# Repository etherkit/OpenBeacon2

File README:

Documentation for the OpenBeacon Mini Multimode MEPT, which is based on the OpenBeacon project.

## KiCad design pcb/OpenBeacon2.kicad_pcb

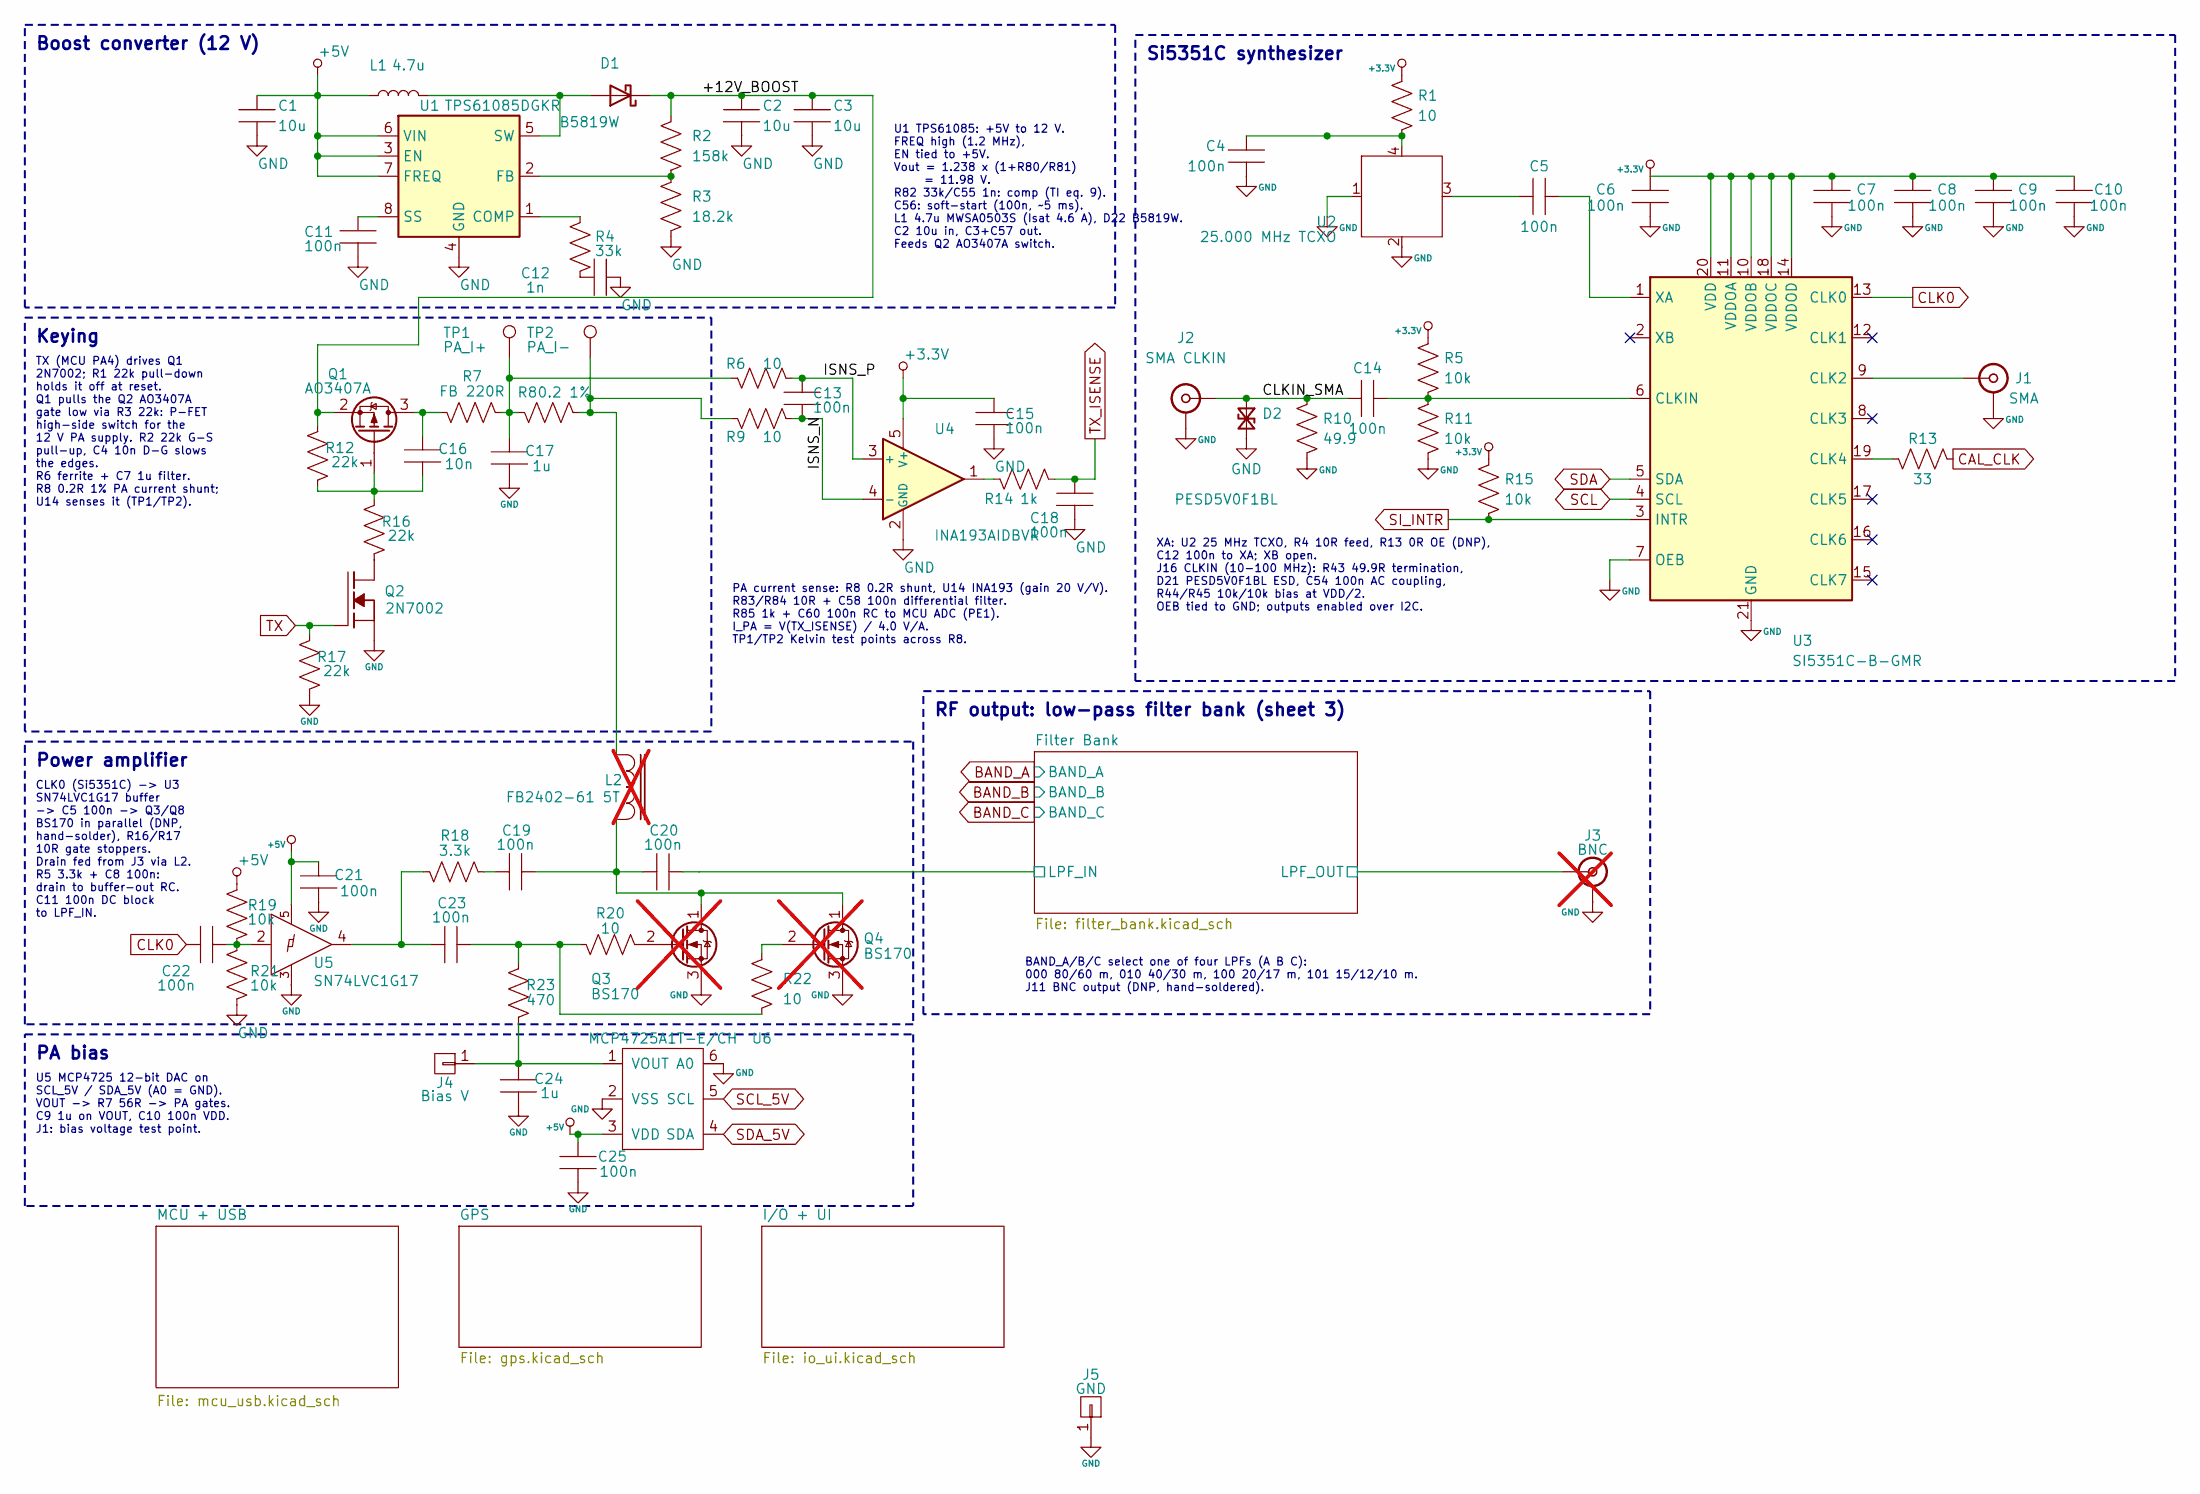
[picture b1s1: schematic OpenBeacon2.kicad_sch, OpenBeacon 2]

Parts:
C1: 10u; C_0805_2012Metric; MPN CL21A106KAYNNNE; LCSC C15850
C2, C3: 10u; C_1206_3216Metric; MPN CL31A106KBHNNNE; LCSC C13585
C4, C5, C19, C20, C21, C23, C25: 100n; C_0805_2012Metric; MPN CC0805KRX7R9BB104; LCSC C49678
C6: 100n; C_0402_1005Metric; MPN CL05B104KO5NNNC; LCSC C1525
C7, C8, C9, C10, C14: 100n; C_0603_1608Metric; MPN CL10B104KB8NNNC; LCSC C1591
C11, C13, C15, C18, C22: 100n; C_0603_1608Metric; MPN CC0603KRX7R9BB104; LCSC C14663
C12: 1n; C_0603_1608Metric; MPN CL10B102KB8NNNC; LCSC C1588
C16: 10n; C_0805_2012Metric; MPN CL21B103KBANNNC; LCSC C1710
C17, C24: 1u; C_0805_2012Metric; MPN CL21B105KBFNNNE; LCSC C28323
D1: B5819W; D_SOD-123; MPN B5819W SL; LCSC C8598
D2: PESD5V0F1BL; D_SOD-882; MPN PESD5V0F1BL,315; LCSC C45961
J1: SMA; SMA-ENDLAUNCH; MPN BWSMA-KE-P001; LCSC C496550
J2: SMA CLKIN; SMA-ENDLAUNCH; MPN BWSMA-KE-P001; LCSC C496550
J3: BNC; BNC-AMPHENOL-31-5431-10RFX; MPN 031-5431-10RFX; LCSC C6956217; not fitted
J4: Bias V; Measurement_Point_Square-TH_Small
J5: GND; Measurement_Point_Square-TH_Small
L1: 4.7u; L_Sunlord_MWSA0503S; MPN MWSA0503S-4R7MT; LCSC C408410
L2: FB2402-61 5T; BN2402; MPN 2843002402; not fitted
Q1: AO3407A; SOT23-MMBT440X; MPN AO3407A; LCSC C15155
Q2: 2N7002; SOT23-2N7002; MPN 2N7002; LCSC C8545
Q3, Q4: BS170; TO-92_Inline; MPN BS170; LCSC C111691; not fitted
R1: 10; R_0805_2012Metric; MPN 0805W8F100JT5E; LCSC C17415
R2: 158k; R_0603_1608Metric; MPN 0603WAF1583T5E; LCSC C22883
R3: 18.2k; R_0603_1608Metric; MPN 0603WAF1822T5E; LCSC C22892
R4: 33k; R_0603_1608Metric; MPN 0603WAF3302T5E; LCSC C4216
R5, R11, R15, R19, R21: 10k; R_0603_1608Metric; MPN 0603WAF1002T5E; LCSC C25804
R6, R9, R20, R22: 10; R_0603_1608Metric; MPN 0603WAF100JT5E; LCSC C22859
R7: FB 220R; L_0603_1608Metric; MPN BLM18PG221SN1D; LCSC C80165
R8: 0.2 1%; R_0805_2012Metric; MPN 0805W8F200LT5E; LCSC C44051
R10: 49.9; R_0603_1608Metric; MPN 0603WAF499JT5E; LCSC C23185
R12, R16, R17: 22k; R_0805_2012Metric; MPN 0805W8F2202T5E; LCSC C17560
R13: 33; R_0603_1608Metric; MPN 0603WAF330JT5E; LCSC C23140
R14: 1k; R_0603_1608Metric; MPN 0603WAF1001T5E; LCSC C21190
R18: 3.3k; R_0805_2012Metric; MPN 0805W8F3301T5E; LCSC C26010
R23: 470; R_0805_2012Metric; MPN 0805W8F4700T5E; LCSC C17710
TP1: PA_I+; Measurement_Point_Square-TH_Small
TP2: PA_I-; Measurement_Point_Square-TH_Small
U1: TPS61085DGKR; VSSOP-8_3x3mm_P0.65mm; MPN TPS61085DGKR; LCSC C113659
U2: 25.000 MHz TCXO; ASTX-H11-25.000MHZ-T; MPN OW2EL89CENUXK7YLC-25M; LCSC C48888230
U3: SI5351C-B-GMR; QFN-20-1EP_4x4mm_P0.5mm_EP2.7x2.7mm; MPN SI5351C-B-GMR; LCSC C2649375
U4: INA193AIDBVR; SOT-23-5; MPN INA193AIDBVR; LCSC C19548
U5: SN74LVC1G17; SOT23-5; MPN SN74LVC1G17DBVR; LCSC C7836
U6: MCP4725A1T-E/CH; SOT23-6; MPN MCP4725A1T-E/CH; LCSC C61423

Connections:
+3.3V: C6.1, C7.1, C8.1, C9.1, C10.1, C15.1, R1.1, R5.1, R15.1, U3.10 (VDDOB), U3.11 (VDDOA), U3.14 (VDDOD), U3.18 (VDDOC), U3.20 (VDD), U4.5 (V+); also elsewhere on the board
+5V: C1.1, C21.1, C25.1, L1.1, R19.1, U1.3 (EN), U1.6 (VIN), U1.7 (FREQ), U5.5 (VCC), U6.3 (VDD); also elsewhere on the board
/+12V_BOOST: C2.1, C3.1, D1.1 (K), Q1.2 (S), R2.1, R12.1
/CLKIN_SMA: C14.1, D2.1 (A1), J2.1 (In), R10.1
/Filter Bank/LPF_IN: C20.1; also elsewhere on the board
/Filter Bank/LPF_OUT: J3.1 (In); also elsewhere on the board
/ISNS_N: C13.2, R9.2, U4.4 (-)
/ISNS_P: C13.1, R6.2, U4.3 (+)
CAL_CLK: R13.2; also elsewhere on the board
CLK0: C22.1, U3.13 (CLK0)
GND: C1.2, C2.2, C3.2, C4.2, C6.2, C7.2, C8.2, C9.2, C10.2, C11.2, C12.2, C15.2, C17.2, C18.2, C21.2, C24.2, C25.2, D2.2 (A2), J1.2 (Ext), J2.2 (Ext), J3.2 (Ext), J5.1, Q2.1 (S), Q3.3 (S), Q4.3 (S), R3.2, R10.2, R11.2, R17.2, R21.2, U1.4 (GND), U2.1 (GND), U2.2 (GND), U3.7 (OEB), U3.21 (GND), U4.2 (GND), U5.3 (GND), U6.2 (VSS), U6.6 (A0); also elsewhere on the board
unnamed: C12.1, R4.2
unnamed: C17.1, R6.1, R7.1, R8.2, TP1.1
unnamed: C19.2, R18.1
unnamed: C22.2, R19.2, R21.1, U5.2
unnamed: C23.1, R20.1, R22.2, R23.1
unnamed: C23.2, R18.2, U5.4
unnamed: D1.2 (A), L1.2, U1.5 (SW)
unnamed: J1.1 (In), U3.9 (CLK2)
unnamed: C24.1, J4.1, R23.2, U6.1 (VOUT)
unnamed: L2.1, R8.1, R9.1, TP2.1
unnamed: C16.1, Q1.3 (D), R7.2
unnamed: C16.2, Q1.1 (G), R12.2, R16.1
unnamed: Q2.3 (D), R16.2
unnamed: C19.1, C20.2, L2.2, Q3.1 (D), Q4.1 (D)
unnamed: Q3.2 (G), R20.2
unnamed: Q4.2 (G), R22.1
unnamed: R14.1, U4.1
unnamed: R4.1, U1.1 (COMP)
unnamed: R2.2, R3.1, U1.2 (FB)
unnamed: C11.1, U1.8 (SS)
unnamed: C5.1, U2.3 (OUT)
unnamed: C4.1, R1.2, U2.4 (VDD)
unnamed: R13.1, U3.19 (CLK4)
unnamed: C14.2, R5.2, R11.1, U3.6 (CLKIN)
unnamed: C5.2, U3.1 (XA)
SCL: U3.4 (SCL); also elsewhere on the board
SCL_5V: U6.5 (SCL); also elsewhere on the board
SDA: U3.5 (SDA); also elsewhere on the board
SDA_5V: U6.4 (SDA); also elsewhere on the board
SI_INTR: R15.2, U3.3 (INTR); also elsewhere on the board
TX: Q2.2 (G), R17.1; also elsewhere on the board
TX_ISENSE: C18.1, R14.2; also elsewhere on the board

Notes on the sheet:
Boost converter (12 V)
Keying
TX (MCU PA4) drives Q1 2N7002; R1 22k pull-down holds it off at reset. Q1 pulls the Q2 AO3407A gate low via R3 22k: P-FET high-side switch for the 12 V PA supply. R2 22k G-S pull-up, C4 10n D-G slows the edges. R6 ferrite + C7 1u filter. R8 0.2R 1% PA current shunt; U14 senses it (TP1/TP2).
Power amplifier
CLK0 (Si5351C) -> U3 SN74LVC1G17 buffer -> C5 100n -> Q3/Q8 BS170 in parallel (DNP, hand-solder), R16/R17 10R gate stoppers. Drain fed from J3 via L2. R5 3.3k + C8 100n: drain to buffer-out RC. C11 100n DC block to LPF_IN.
PA bias
U5 MCP4725 12-bit DAC on SCL_5V / SDA_5V (A0 = GND). VOUT -> R7 56R -> PA gates. C9 1u on VOUT, C10 100n VDD. J1: bias voltage test point.
Si5351C synthesizer
XA: U2 25 MHz TCXO, R4 10R feed, R13 0R OE (DNP), C12 100n to XA; XB open. J16 CLKIN (10-100 MHz): R43 49.9R termination, D21 PESD5V0F1BL ESD, C54 100n AC coupling, R44/R45 10k/10k bias at VDD/2. OEB tied to GND; outputs enabled over I2C.
RF output: low-pass filter bank (sheet 3)
BAND_A/B/C select one of four LPFs (A B C): 000 80/60 m, 010 40/30 m, 100 20/17 m, 101 15/12/10 m. J11 BNC output (DNP, hand-soldered).
U1 TPS61085: +5V to 12 V. FREQ high (1.2 MHz), EN tied to +5V. Vout = 1.238 x (1+R80/R81) = 11.98 V. R82 33k/C55 1n: comp (TI eq. 9). C56: soft-start (100n, ~5 ms). L1 4.7u MWSA0503S (Isat 4.6 A), D22 B5819W. C2 10u in, C3+C57 out. Feeds Q2 AO3407A switch.
PA current sense: R8 0.2R shunt, U14 INA193 (gain 20 V/V). R83/R84 10R + C58 100n differential filter. R85 1k + C60 100n RC to MCU ADC (PE1). I_PA = V(TX_ISENSE) / 4.0 V/A. TP1/TP2 Kelvin test points across R8.

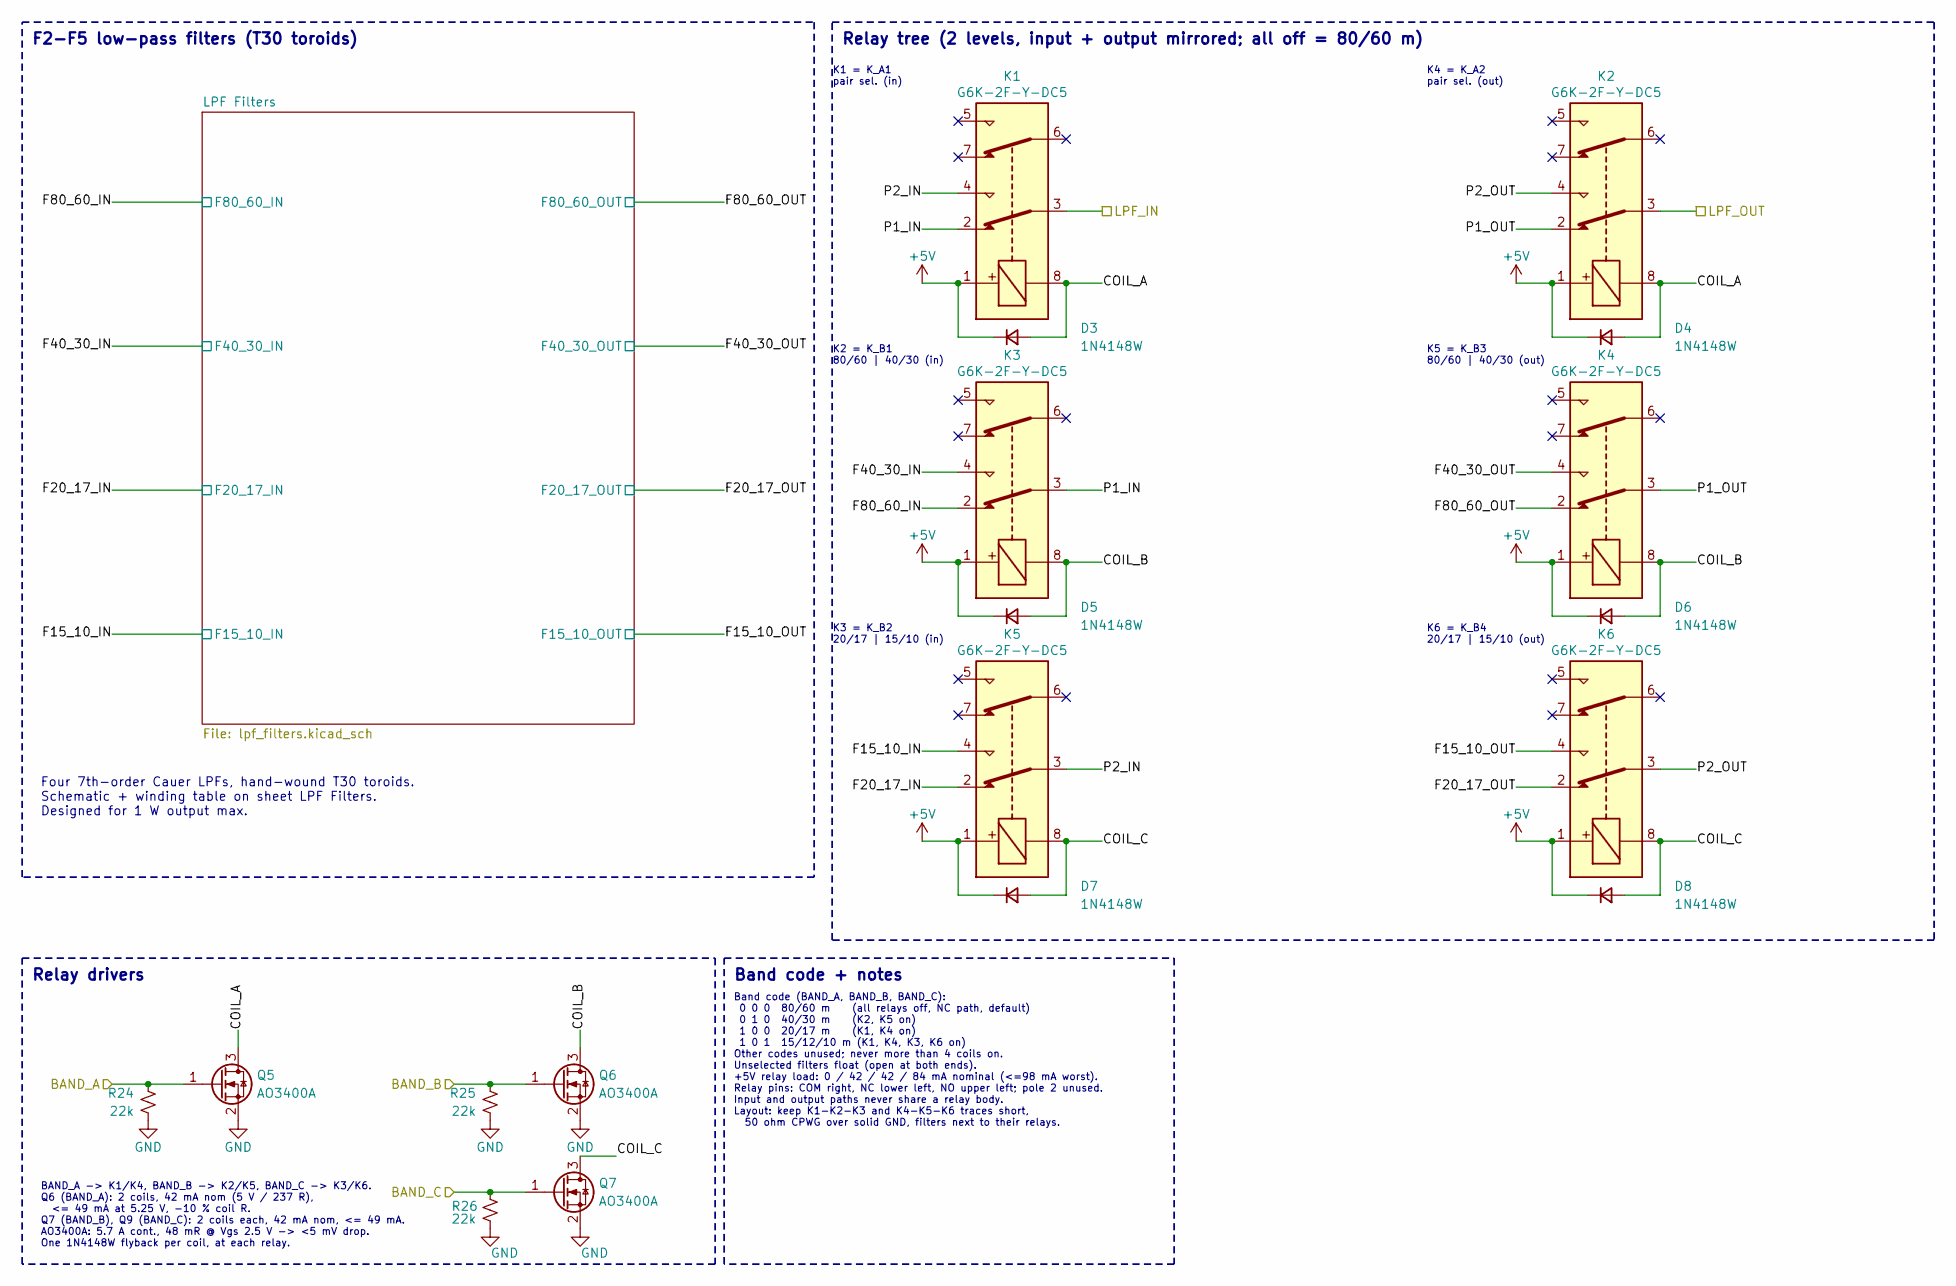
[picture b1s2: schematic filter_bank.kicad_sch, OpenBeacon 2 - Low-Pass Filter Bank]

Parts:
D3, D4, D5, D6, D7, D8: 1N4148W; D_SOD-123; MPN 1N4148W; LCSC C81598
K1, K2, K3, K4, K5, K6: G6K-2F-Y-DC5; Relay_DPDT_Omron_G6K-2F-Y; MPN G6K-2F-Y-DC5; LCSC C326376
Q5, Q6, Q7: AO3400A; SOT-23; MPN AO3400A; LCSC C20917
R24, R25, R26: 22k; R_0603_1608Metric; MPN 0603WAF2202T5E; LCSC C31850

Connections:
+5V: D3.1 (K), D4.1 (K), D5.1 (K), D6.1 (K), D7.1 (K), D8.1 (K), K1.1, K2.1, K3.1, K4.1, K5.1, K6.1; also elsewhere on the board
/Filter Bank/COIL_A: D3.2 (A), D4.2 (A), K1.8, K2.8, Q5.3 (D)
/Filter Bank/COIL_B: D5.2 (A), D6.2 (A), K3.8, K4.8, Q6.3 (D)
/Filter Bank/COIL_C: D7.2 (A), D8.2 (A), K5.8, K6.8, Q7.3 (D)
/Filter Bank/F15_10_IN: K5.4; also elsewhere on the board
/Filter Bank/F15_10_OUT: K6.4; also elsewhere on the board
/Filter Bank/F20_17_IN: K5.2; also elsewhere on the board
/Filter Bank/F20_17_OUT: K6.2; also elsewhere on the board
/Filter Bank/F40_30_IN: K3.4; also elsewhere on the board
/Filter Bank/F40_30_OUT: K4.4; also elsewhere on the board
/Filter Bank/F80_60_IN: K3.2; also elsewhere on the board
/Filter Bank/F80_60_OUT: K4.2; also elsewhere on the board
/Filter Bank/LPF_IN: K1.3; also elsewhere on the board
/Filter Bank/LPF_OUT: K2.3; also elsewhere on the board
/Filter Bank/P1_IN: K1.2, K3.3
/Filter Bank/P1_OUT: K2.2, K4.3
/Filter Bank/P2_IN: K1.4, K5.3
/Filter Bank/P2_OUT: K2.4, K6.3
BAND_A: Q5.1 (G), R24.1; also elsewhere on the board
BAND_B: Q6.1 (G), R25.1; also elsewhere on the board
BAND_C: Q7.1 (G), R26.1; also elsewhere on the board
GND: Q5.2 (S), Q6.2 (S), Q7.2 (S), R24.2, R25.2, R26.2; also elsewhere on the board

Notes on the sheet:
Relay tree (2 levels, input + output mirrored; all off = 80/60 m)
K1 = K_A1 pair sel. (in)
K2 = K_B1 80/60 | 40/30 (in)
K3 = K_B2 20/17 | 15/10 (in)
K4 = K_A2 pair sel. (out)
K5 = K_B3 80/60 | 40/30 (out)
K6 = K_B4 20/17 | 15/10 (out)
Relay drivers
Band code + notes
BAND_A -> K1/K4, BAND_B -> K2/K5, BAND_C -> K3/K6. Q6 (BAND_A): 2 coils, 42 mA nom (5 V / 237 R), <= 49 mA at 5.25 V, -10 % coil R. Q7 (BAND_B), Q9 (BAND_C): 2 coils each, 42 mA nom, <= 49 mA. AO3400A: 5.7 A cont., 48 mR @ Vgs 2.5 V -> <5 mV drop. One 1N4148W flyback per coil, at each relay.
Band code (BAND_A, BAND_B, BAND_C): 0 0 0 80/60 m (all relays off, NC path, default) 0 1 0 40/30 m (K2, K5 on) 1 0 0 20/17 m (K1, K4 on) 1 0 1 15/12/10 m (K1, K4, K3, K6 on) Other codes unused; never more than 4 coils on. Unselected filters float (open at both ends). +5V relay load: 0 / 42 / 42 / 8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
F2-F5 low-pass filters (T30 toroids)
Four 7th-order Cauer LPFs, hand-wound T30 toroids. Schematic + winding table on sheet LPF Filters. Designed for 1 W output max.

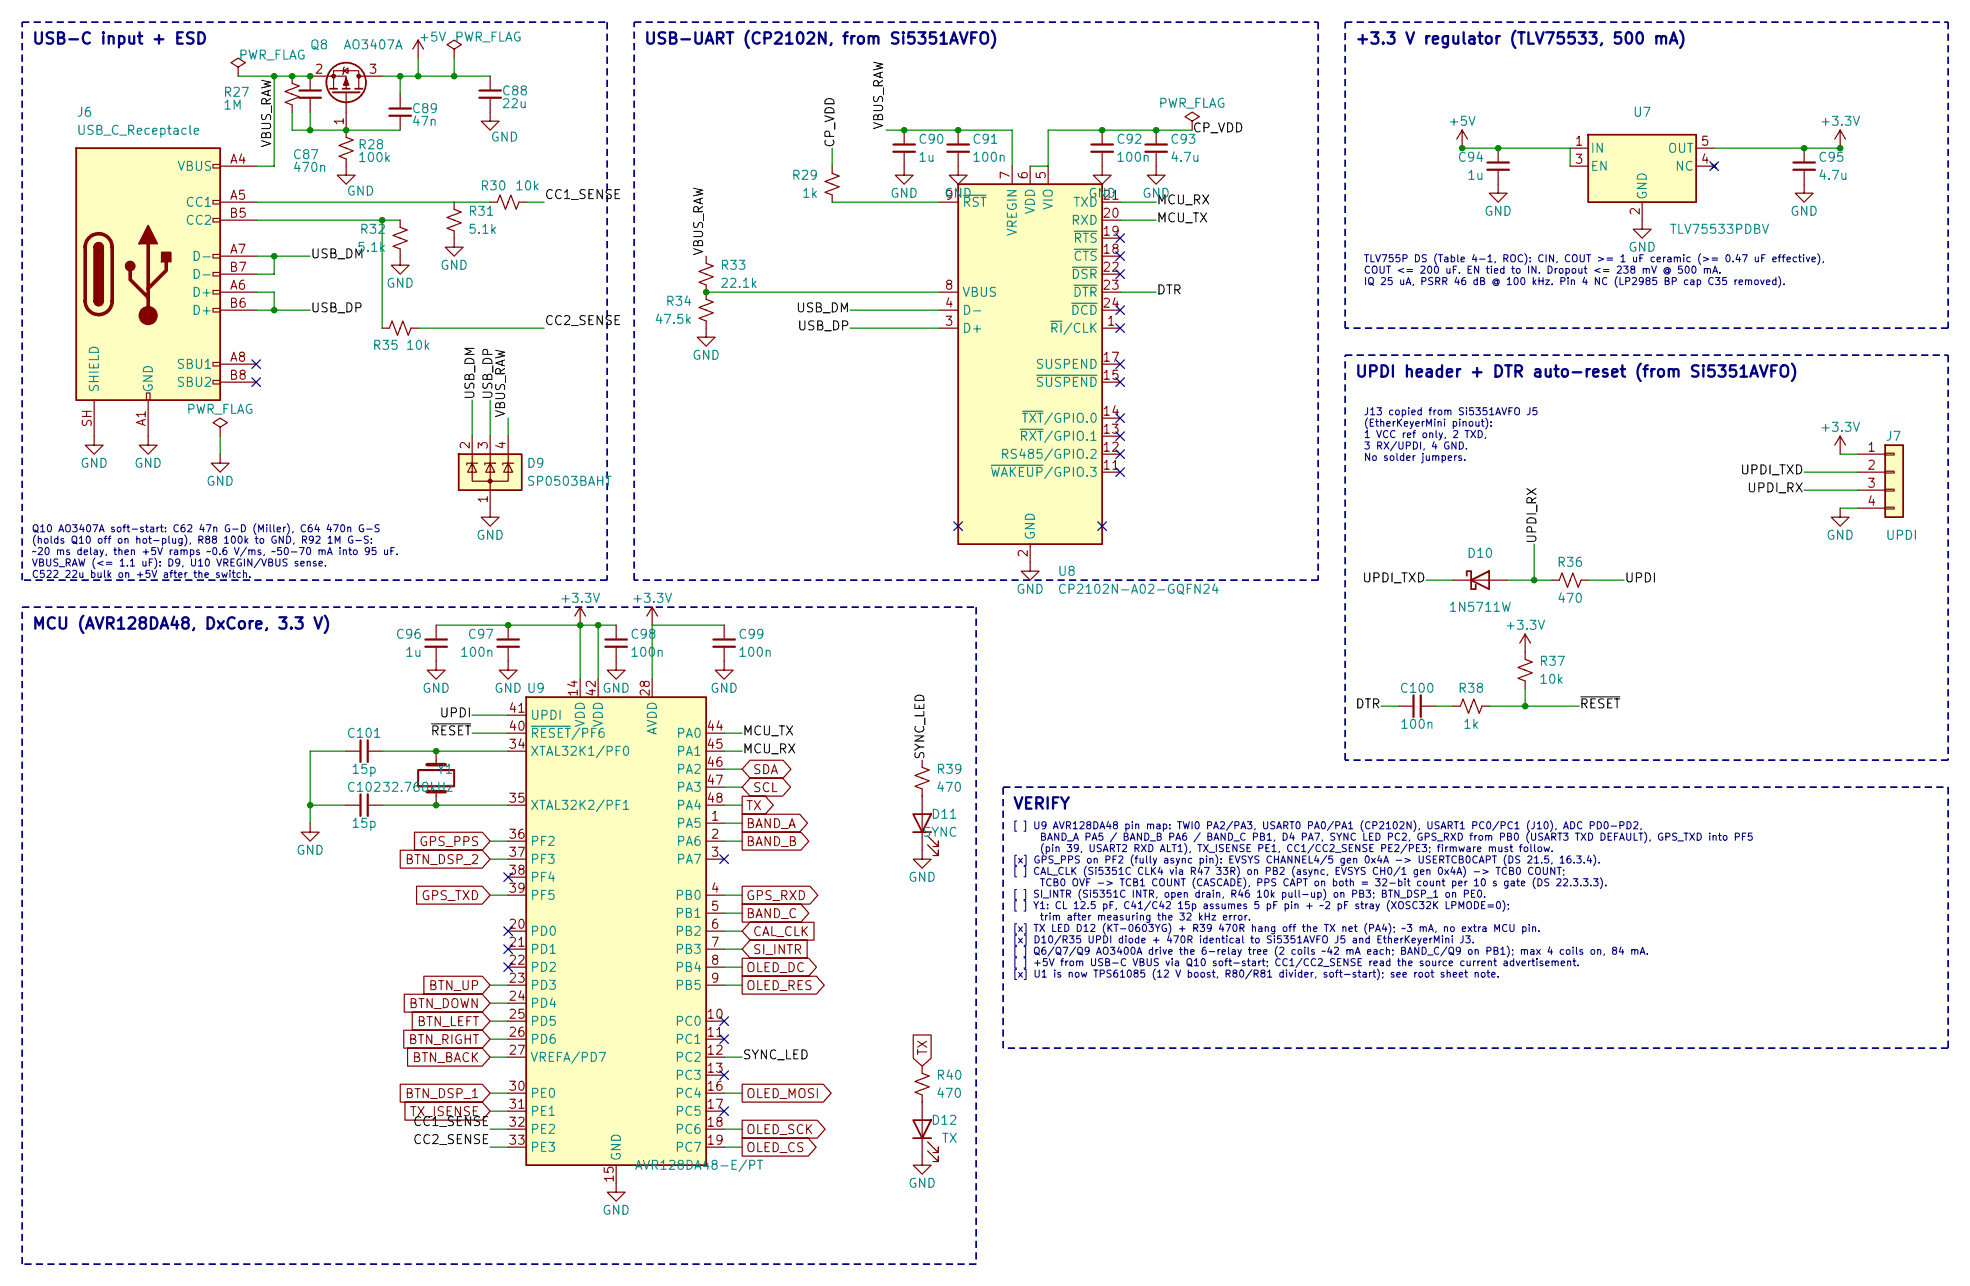
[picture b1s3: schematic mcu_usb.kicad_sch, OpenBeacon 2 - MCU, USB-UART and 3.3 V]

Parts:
C87: 470n; C_0603_1608Metric; MPN CL10B474KA8NNNC; LCSC C1623
C88: 22u; C_1206_3216Metric; MPN CL31A226KAHNNNE; LCSC C12891
C89: 47n; C_0603_1608Metric; MPN CL10B473KB8NNNC; LCSC C1622
C90: 1u; C_0402_1005Metric; MPN CL10A105KB8NNNC; LCSC C15849
C91, C92, C97: 100n; C_0402_1005Metric; MPN CL05B104KO5NNNC; LCSC C1525
C93, C95: 4.7u; C_0402_1005Metric; MPN CL05A475MP5NRNC; LCSC C23733
C94, C96: 1u; C_0805_2012Metric; MPN CL21B105KBFNNNE; LCSC C28323
C98, C99: 100n; C_0603_1608Metric; MPN CC0603KRX7R9BB104; LCSC C14663
C100: 100n; C_0805_2012Metric; MPN CC0805KRX7R9BB104; LCSC C49678
C101, C102: 15p; C_0603_1608Metric; MPN CL10C150JB8NNNC; LCSC C1644
D9: SP0503BAHT; SOT-143; MPN SP0503BAHTG; LCSC C7074
D10: 1N5711W; D_SOD-123; MPN 1N5711W-7-F; LCSC C154843
D11: SYNC; LED_0603_1608Metric; MPN KT-0603Y; LCSC C2287
D12: TX; LED_0603_1608Metric; MPN KT-0603YG; LCSC C2289
J6: USB_C_Receptacle; USB_C_Receptacle_HCTL_HC-TYPE-C-16P-01A; MPN HC-TYPE-C-16P-01A; LCSC C2894897
J7: UPDI; PinHeader_1x04_P2.54mm_Vertical; MPN B-2100S04P-A110; LCSC C124378
Q8: AO3407A; SOT-23; MPN AO3407A; LCSC C15155
R27: 1M; R_0603_1608Metric; MPN 0603WAF1004T5E; LCSC C22935
R28: 100k; R_0603_1608Metric; MPN 0603WAF1003T5E; LCSC C25803
R29, R38: 1k; R_0603_1608Metric; MPN 0603WAF1001T5E; LCSC C21190
R30, R35: 10k; R_0603_1608Metric; MPN 0603WAF1002T5E; LCSC C25804
R31, R32: 5.1k; R_0603_1608Metric; MPN 0603WAF5101T5E; LCSC C23186
R33: 22.1k; R_0603_1608Metric; MPN RC0603FR-0722K1L; LCSC C137768
R34: 47.5k; R_0603_1608Metric; MPN FRC0603F4752TS; LCSC C2933225
R36, R39, R40: 470; R_0603_1608Metric; MPN 0603WAF4700T5E; LCSC C23179
R37: 10k; R_0805_2012Metric; MPN 0805W8F1002T5E; LCSC C17414
U7: TLV75533PDBV; SOT-23-5; MPN TLV75533PDBVR; LCSC C404027
U8: CP2102N-A02-GQFN24; QFN-24-1EP_4x4mm_P0.5mm_EP2.6x2.6mm; MPN CP2102N-A02-GQFN24R; LCSC C969151
U9: AVR128DA48-E/PT; TQFP-48_7x7mm_P0.5mm; MPN AVR128DA48-E/PT; LCSC C5227775
Y1: 32.768kHz; Crystal_SMD_3215-2Pin_3.2x1.5mm; MPN Q13FC13500004; LCSC C32346

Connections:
+3.3V: C95.1, C96.1, C97.1, C98.1, C99.1, J7.1, R37.1, U7.5 (OUT), U9.14 (VDD), U9.28 (AVDD), U9.42 (VDD); also elsewhere on the board
+5V: C88.1, C89.1, C94.1, Q8.3 (D), U7.1 (IN), U7.3 (EN); also elsewhere on the board
/MCU + USB/CC1_SENSE: R30.2, U9.32 (PE2)
/MCU + USB/CC2_SENSE: R35.2, U9.33 (PE3)
/MCU + USB/CP_VDD: C92.1, C93.1, R29.1, U8.5 (VIO), U8.6 (VDD)
/MCU + USB/DTR: C100.1, U8.23 (~DTR)
/MCU + USB/MCU_RX: U8.21 (TXD), U9.45 (PA1)
/MCU + USB/MCU_TX: U8.20 (RXD), U9.44 (PA0)
/MCU + USB/SYNC_LED: R39.1, U9.12 (PC2)
/MCU + USB/UPDI: R36.2, U9.41 (UPDI)
/MCU + USB/UPDI_RX: D10.2 (A), J7.3, R36.1
/MCU + USB/UPDI_TXD: D10.1 (K), J7.2
/MCU + USB/USB_DM: D9.2 (K), J6.A7 (D-), J6.B7 (D-), U8.4 (D-)
/MCU + USB/USB_DP: D9.3 (K), J6.A6 (D+), J6.B6 (D+), U8.3 (D+)
/MCU + USB/VBUS_RAW: C87.1, C90.1, C91.1, D9.4 (K), J6.A4 (VBUS), J6.A9 (VBUS), J6.B4 (VBUS), J6.B9 (VBUS), Q8.2 (S), R27.1, R33.1, U8.7 (VREGIN)
/MCU + USB/~RESET: R37.2, R38.2, U9.40 (~RESET/PF6)
BAND_A: U9.1 (PA5); also elsewhere on the board
BAND_B: U9.2 (PA6); also elsewhere on the board
BAND_C: U9.5 (PB1); also elsewhere on the board
BTN_BACK: U9.27 (VREFA/PD7); also elsewhere on the board
BTN_DOWN: U9.24 (PD4); also elsewhere on the board
BTN_DSP_1: U9.30 (PE0); also elsewhere on the board
BTN_DSP_2: U9.37 (PF3); also elsewhere on the board
BTN_LEFT: U9.25 (PD5); also elsewhere on the board
BTN_RIGHT: U9.26 (PD6); also elsewhere on the board
BTN_UP: U9.23 (PD3); also elsewhere on the board
CAL_CLK: U9.6 (PB2); also elsewhere on the board
GND: C88.2, C90.2, C91.2, C92.2, C93.2, C94.2, C95.2, C96.2, C97.2, C98.2, C99.2, C101.1, C102.1, D9.1 (A), D11.1 (K), D12.1 (K), J6.A1 (GND), J6.A12 (GND), J6.B1 (GND), J6.B12 (GND), J6.SH (SHIELD), J7.4, R28.2, R31.2, R32.2, R34.2, U7.2 (GND), U8.2 (GND), U8.25 (GND), U9.15 (GND), U9.29 (GND), U9.43 (GND); also elsewhere on the board
GPS_PPS: U9.36 (PF2); also elsewhere on the board
GPS_RXD: U9.4 (PB0); also elsewhere on the board
GPS_TXD: U9.39 (PF5); also elsewhere on the board
unnamed: C100.2, R38.1
unnamed: D11.2 (A), R39.2
unnamed: D12.2 (A), R40.2
unnamed: J6.A5 (CC1), R30.1, R31.1
unnamed: J6.B5 (CC2), R32.1, R35.1
unnamed: C87.2, C89.2, Q8.1 (G), R27.2, R28.1
unnamed: R33.2, R34.1, U8.8 (VBUS)
unnamed: R29.2, U8.9 (~RST)
unnamed: C101.2, U9.34 (XTAL32K1/PF0), Y1.2
unnamed: C102.2, U9.35 (XTAL32K2/PF1), Y1.1
OLED_CS: U9.19 (PC7); also elsewhere on the board
OLED_DC: U9.8 (PB4); also elsewhere on the board
OLED_MOSI: U9.16 (PC4); also elsewhere on the board
OLED_RES: U9.9 (PB5); also elsewhere on the board
OLED_SCK: U9.18 (PC6); also elsewhere on the board
SCL: U9.47 (PA3); also elsewhere on the board
SDA: U9.46 (PA2); also elsewhere on the board
SI_INTR: U9.7 (PB3); also elsewhere on the board
TX: R40.1, U9.48 (PA4); also elsewhere on the board
TX_ISENSE: U9.31 (PE1); also elsewhere on the board

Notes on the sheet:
USB-C input + ESD
USB-UART (CP2102N, from Si5351AVFO)
+3.3 V regulator (TLV75533, 500 mA)
TLV755P DS (Table 4-1, ROC): CIN, COUT >= 1 uF ceramic (>= 0.47 uF effective), COUT <= 200 uF. EN tied to IN. Dropout <= 238 mV @ 500 mA. IQ 25 uA, PSRR 46 dB @ 100 kHz. Pin 4 NC (LP2985 BP cap C35 removed).
UPDI header + DTR auto-reset (from Si5351AVFO)
J13 copied from Si5351AVFO J5 (EtherKeyerMini pinout): 1 VCC ref only, 2 TXD, 3 RX/UPDI, 4 GND. No solder jumpers.
MCU (AVR128DA48, DxCore, 3.3 V)
VERIFY
[ ] U9 AVR128DA48 pin map: TWI0 PA2/PA3, USART0 PA0/PA1 (CP2102N), USART1 PC0/PC1 (J10), ADC PD0-PD2, BAND_A PA5 / BAND_B PA6 / BAND_C PB1, D4 PA7, SYNC LED PC2, GPS_RXD from PB0 (USART3 TXD DEFAULT), GPS_TXD into PF5 (pin 39, USART2 RXD ALT1), TX_ISENSE PE1, CC1/CC2_SENSE PE2/PE3; firmware must fo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
Q10 AO3407A soft-start: C62 47n G-D (Miller), C64 470n G-S (holds Q10 off on hot-plug), R88 100k to GND, R92 1M G-S: ~20 ms delay, then +5V ramps ~0.6 V/ms, ~50-70 mA into 95 uF. VBUS_RAW (<= 1.1 uF): D9, U10 VREGIN/VBUS sense. C522 22u bulk on +5V after the switch.

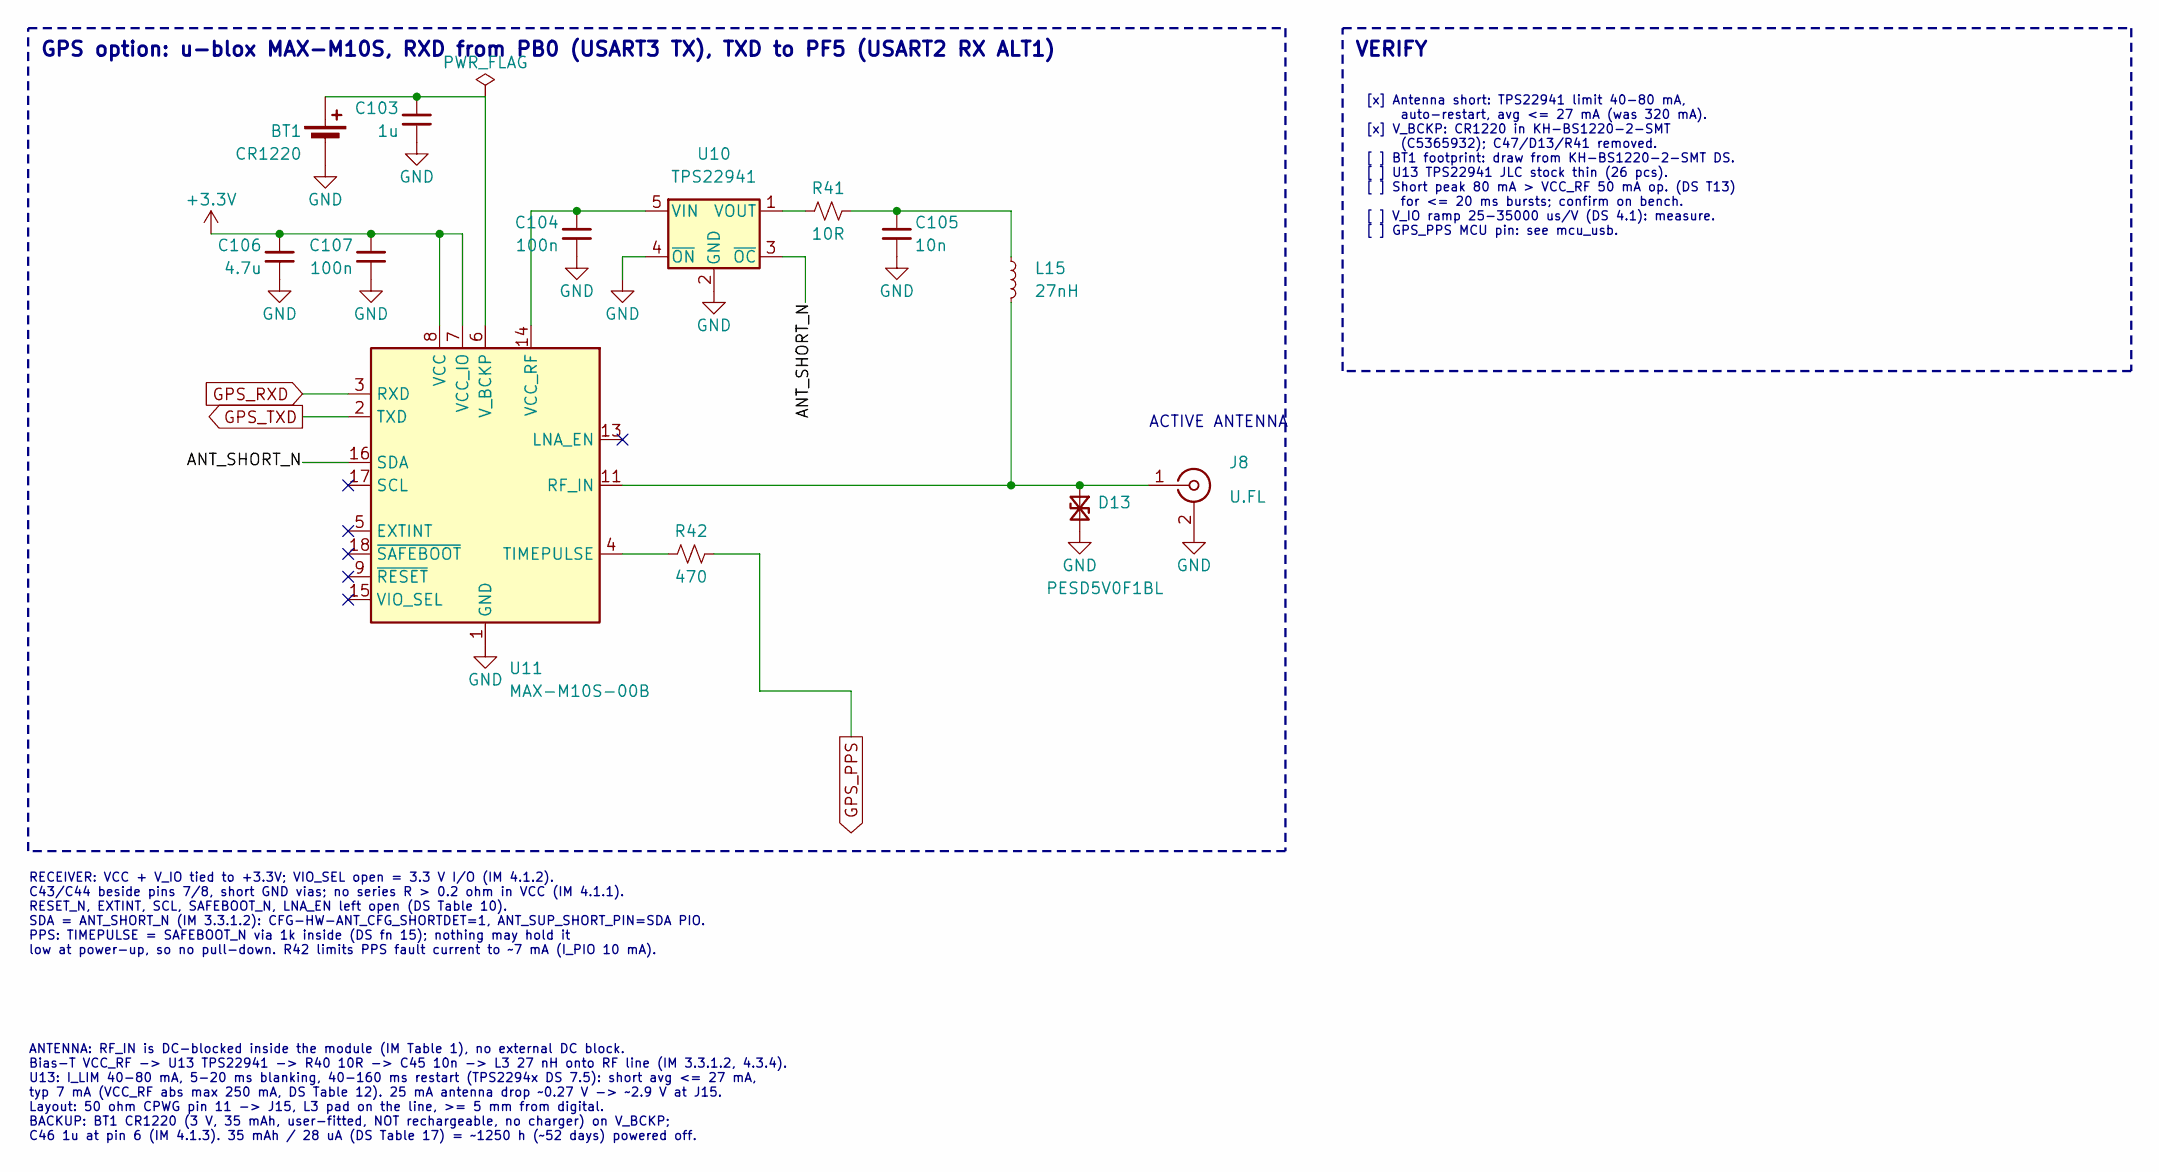
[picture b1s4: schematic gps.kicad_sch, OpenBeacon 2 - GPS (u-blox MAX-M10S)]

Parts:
BT1: CR1220; BAT-SMD_KH-CR1220-2; MPN KH-BS1220-2-SMT; LCSC C5365932
C103: 1u; C_0402_1005Metric; MPN CL05A105KA5NQNC; LCSC C52923
C104, C107: 100n; C_0603_1608Metric; MPN CL10B104KB8NNNC; LCSC C1591
C105: 10n; C_0603_1608Metric; MPN CC0603KRX7R9BB103; LCSC C100042
C106: 4.7u; C_0805_2012Metric; MPN CL21A475KAQNNNE; LCSC C1779
D13: PESD5V0F1BL; D_SOD-882; MPN PESD5V0F1BL,315; LCSC C45961
J8: U.FL; U.FL_Hirose_U.FL-R-SMT-1_Vertical; MPN U.FL-R-SMT-1(80); LCSC C88374
L15: 27nH; L_0402_1005Metric; MPN LQG15HS27NJ02D; LCSC C12669
R41: 10R; R_1206_3216Metric; MPN 1206W4F100JT5E; LCSC C17903
R42: 470; R_0603_1608Metric; MPN 0603WAF4700T5E; LCSC C23179
U10: TPS22941; SOT-353_SC-70-5; MPN TPS22941DCKR; LCSC C2653762
U11: MAX-M10S-00B; ublox_MAX; MPN MAX-M10S-00B; LCSC C4153167

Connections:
+3.3V: C106.1, C107.1, U11.7 (VCC_IO), U11.8 (VCC); also elsewhere on the board
/GPS/ANT_SHORT_N: U10.3 (~OC), U11.16 (SDA)
GND: BT1.2 (-), C103.2, C104.2, C105.2, C106.2, C107.2, D13.2 (A2), J8.2 (Ext), U10.2 (GND), U10.4 (~ON), U11.1 (GND), U11.10 (GND), U11.12 (GND); also elsewhere on the board
GPS_PPS: R42.2; also elsewhere on the board
GPS_RXD: U11.3 (RXD); also elsewhere on the board
GPS_TXD: U11.2 (TXD); also elsewhere on the board
unnamed: BT1.1 (+), C103.1, U11.6 (V_BCKP)
unnamed: C105.1, L15.1, R41.2
unnamed: D13.1 (A1), J8.1 (In), L15.2, U11.11 (RF_IN)
unnamed: C104.1, U10.5 (VIN), U11.14 (VCC_RF)
unnamed: R41.1, U10.1 (VOUT)
unnamed: R42.1, U11.4 (TIMEPULSE)

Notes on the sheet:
ACTIVE ANTENNA
GPS option: u-blox MAX-M10S, RXD from PB0 (USART3 TX), TXD to PF5 (USART2 RX ALT1)
RECEIVER: VCC + V_IO tied to +3.3V; VIO_SEL open = 3.3 V I/O (IM 4.1.2). C43/C44 beside pins 7/8, short GND vias; no series R > 0.2 ohm in VCC (IM 4.1.1). RESET_N, EXTINT, SCL, SAFEBOOT_N, LNA_EN left open (DS Table 10). SDA = ANT_SHORT_N (IM 3.3.1.2): CFG-HW-ANT_CFG_SHORTDET=1, ANT_SUP_SHORT_PIN=S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
ANTENNA: RF_IN is DC-blocked inside the module (IM Table 1), no external DC block. Bias-T VCC_RF -> U13 TPS22941 -> R40 10R -> C45 10n -> L3 27 nH onto RF line (IM 3.3.1.2, 4.3.4). U13: I_LIM 40-80 mA, 5-20 ms blanking, 40-160 ms restart (TPS2294x DS 7.5): short avg <= 27 mA, typ 7 mA (VCC_RF abs m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
VERIFY
[x] Antenna short: TPS22941 limit 40-80 mA, auto-restart, avg <= 27 mA (was 320 mA). [x] V_BCKP: CR1220 in KH-BS1220-2-SMT (C5365932); C47/D13/R41 removed. [ ] BT1 footprint: draw from KH-BS1220-2-SMT DS. [ ] U13 TPS22941 JLC stock thin (26 pcs). [ ] Short peak 80 mA > VCC_RF 50 mA op. (DS T13) for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

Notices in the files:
pcb/OpenBeacon2.kicad_pcb:
Creative Commons License 4.0 CC-BY-SA
CC-BY-SA 4.0
pcb/OpenBeacon2.kicad_sch:
Creative Commons License CC-BY-SA
